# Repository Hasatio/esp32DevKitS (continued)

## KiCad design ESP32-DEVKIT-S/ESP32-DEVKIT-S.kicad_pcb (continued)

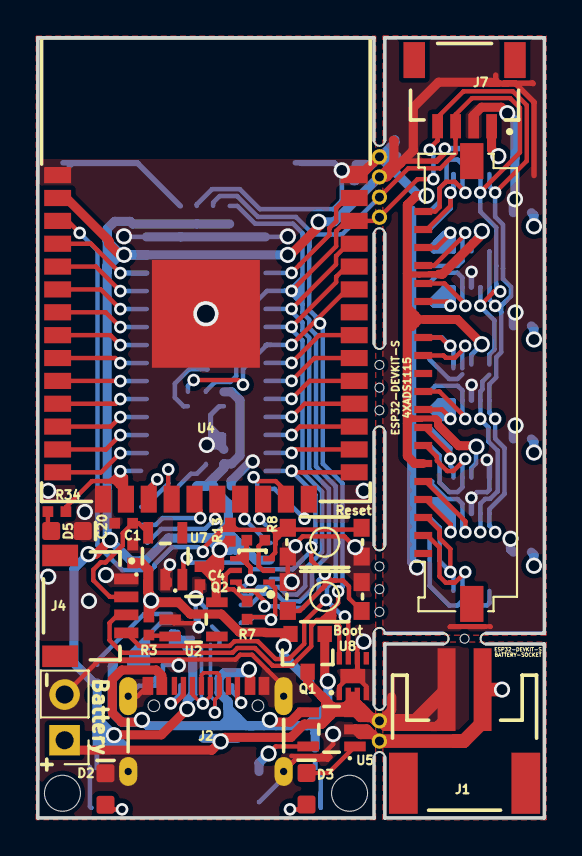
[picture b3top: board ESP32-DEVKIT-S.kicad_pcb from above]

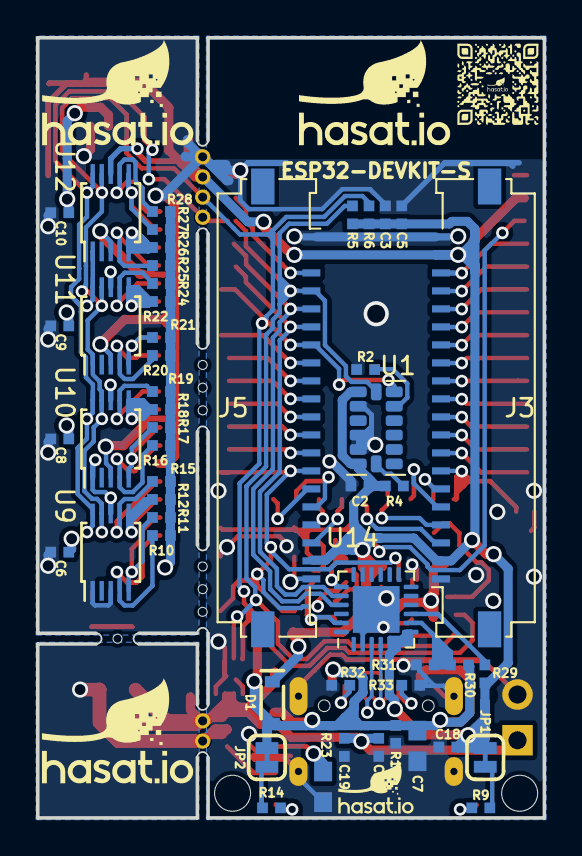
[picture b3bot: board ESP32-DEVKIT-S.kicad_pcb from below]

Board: 2 copper layers, 28.1 x 43.3 mm, 82 parts (51 on the bottom side), 75 nets.

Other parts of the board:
FRAME1: FRAME-LEDGER; CREATIVE_COMMONS
mouse-bite-1mm-slot, mouse-bite-1mm-slot#2: VAL**; mouse-bite-1mm x4
mouse-bite-1mm-slot#3: VAL**; mouse-bite-1mm x2
mouse-bite-1mm-slot#4: VAL**; mouse-bite-1mm 4
mouse-bite-emm-slot: VAL**; mouse-bite-1mm 2

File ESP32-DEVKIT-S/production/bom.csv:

Designator,Footprint,Quantity,Value,LCSC Part #
"_2, ",,2,,
<<<<<<< HEAD
"C1, C10, C11, C14, C2, C3, C8, C9",0402-TIGHT,8,1.0uF,
"C12, C13",0402-TIGHT,2,0.1uF,
"C4, C5",0402-TIGHT,2,10uF,
"C6, C7",0402-TIGHT,2,4.7uF,
D1,SOD-323,1,S4 3A/10V/280mV,
=======
"C1, C10, C2, C20, C3, C6, C8, C9",0402-TIGHT,8,1.0uF,
C12,0402-TIGHT,1,4.7uF,
"C18, C19",0402-TIGHT,2,0.1uF,
"C4, C5",0402-TIGHT,2,10uF,
C7,0603,1,4.7uF,
D1,SOD-323,1,3A/10V/280mV,
>>>>>>> 68af404355b3b751be5d1c865b114c6b0174d70a
D2,LED-0603,1,RED,
D3,LED-0603,1,Yellow,
D5,LED-0603,1,BLUE,
FRAME1,CREATIVE_COMMONS,1,FRAME-LEDGER,
J1,JST-2-SMD,1,JST_2MM_MALE,
J2,USB-C-16P-2LAYER-PADS,1,USB_C_2-LAYER_PADS,
"J3, J5, J6",Molex_200528-0200_1x20-1MP_P1.00mm_Horizontal,3,Conn_01x20,
"J4, J7",JST04_1MM_RA,2,QWIIC_RIGHT_ANGLE,
"JP1, JP2",SMT-JUMPER_2_NC_TRACE_SILK,2,JUMPER-SMT_2_NC_TRACE_SILK,
<<<<<<< HEAD
Q1,SOT23-3,1,DMG2305UX 20V/4.2A/52mΩ/1.4W,
Q2,SC70-6,1,MBT3904DW1T1,
"R1, R26, R3, R4, R7, R8",0402-TIGHT,6,10k,
"R10, R11, R12, R13, R14, R15, R16, R17, R18, R19, R20, R21, R22, R23, R24, R25",0402-TIGHT,16,150k,
"R2, R5, R6",0402-TIGHT,3,4k7,
"R27, R34, R9",0402-TIGHT,3,1k,
R28,0402-TIGHT,1,2.0k,
=======
Q1,SOT23-3,1,20V/4.2A/52mΩ/1.4W,
Q2,SC70-6,1,MBT3904DW1T1,
"R1, R10, R11, R12, R13, R15, R16, R17, R18, R19, R20, R21, R22, R24, R25, R26, R27, R28, R29, R3, R4, R7, R8",0402-TIGHT,23,10k,
"R14, R34, R9",0402-TIGHT,3,1k,
"R2, R5, R6",0402-TIGHT,3,4k7,
R23,0603,1,2.0k,
R30,0402-TIGHT,1,22k,
R31,0402-TIGHT,1,33k,
>>>>>>> 68af404355b3b751be5d1c865b114c6b0174d70a
"R32, R33",0402-TIGHT,2,5.1k,
S1,TACTILE_SWITCH_SMD_4.6X2.8MM,1,Boot,
S2,TACTILE_SWITCH_SMD_4.6X2.8MM,1,Reset,
U1,LGA-14_3x5mm_P0.8mm_LayoutBorder1x6y,1,ADXL345,
<<<<<<< HEAD
"U10, U2",SOT23-5,2,AP2112K-3.3,
U11,DFN-8,1,MAX17048,
U3,ESP-WROOM-32-NARROW,1,>VALUE,
U4,SOT23-5,1,MCP73831,
"U5, U6, U7, U8",TSSOP-10_3x3mm_P0.5mm,4,ADS1115IDGS,
U9,SSOP-10_3.9x4.9mm_P1.00mm,1,CH340K,
=======
"U10, U11, U12, U9",TSSOP-10_3x3mm_P0.5mm,4,ADS1115IDGS,
U14,QFN-24-1EP_4x4mm_P0.5mm_EP2.6x2.6mm,1,CP2102N-Axx-xQFN24,
"U2, U7",SOT23-5,2,AP2112K-3.3,
U4,ESP-WROOM-32-NARROW,1,>VALUE,
U5,SOT23-5,1,MCP73831,
U8,DFN-8,1,MAX17048,
"mouse-bite-1mm-slot_4, mouse-bite-1mm-slot_3",mouse-bite-1mm x4,2,VAL**,
mouse-bite-1mm-slot_2,mouse-bite-1mm x2,1,VAL**,
mouse-bite-1mm-slot,mouse-bite-1mm 4,1,VAL**,
mouse-bite-emm-slot,mouse-bite-1mm 2,1,VAL**,
>>>>>>> 68af404355b3b751be5d1c865b114c6b0174d70a

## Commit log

2023-03-13 13.03.23
2023-03-14 14.03.23
2023-03-15 15.03.23
2023-03-15 add logo and qr
2023-03-15 add battery pin
2023-03-16 17.03.23
    cp2102 yerine ch340 ekledim
2023-03-17 17.03.23
2023-04-22 23.04.23
2023-04-26 add mirror
